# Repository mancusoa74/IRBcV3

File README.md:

# IRBcV3.1

Internet Relay Board Caricatore v3.1

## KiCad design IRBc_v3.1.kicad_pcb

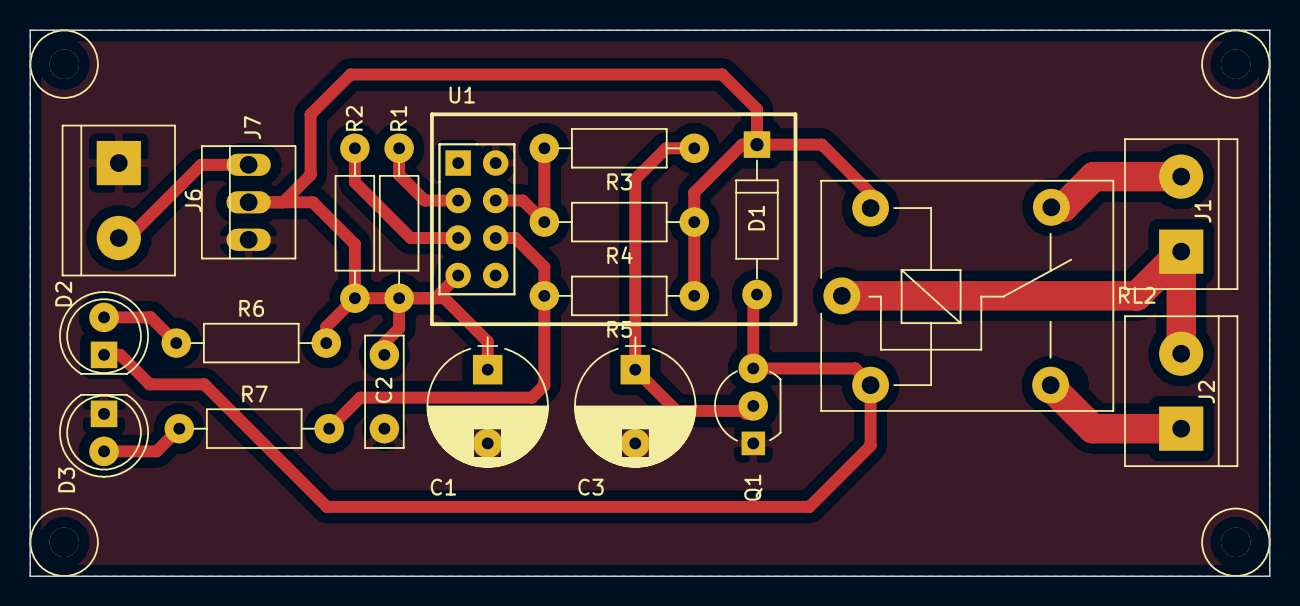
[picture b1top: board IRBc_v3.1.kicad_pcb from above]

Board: 2 copper layers, 84.0 x 37.0 mm, 20 parts (0 on the bottom side), 14 nets.

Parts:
C1: 100uF; CP_Radial_D8.0mm_P5.00mm
C2: 100nF; C_Disc_D7.5mm_W2.5mm_P5.00mm
C3: 220uF; CP_Radial_D8.0mm_P5.00mm
D1: 1N4007; D_A-405_P10.16mm_Horizontal
D2, D3: LED; LED_D5.0mm
J1, J2: bornier2
J6: Caricatore; bornier2
J7: AMS117 module; PINHEAD1-3
Q1: 2N2222; TO-92_Inline_Wide
R1, R2, R3, R4, R5: 2K2; R_Axial_DIN0207_L6.3mm_D2.5mm_P10.16mm_Horizontal
R6, R7: 100; R_Axial_DIN0207_L6.3mm_D2.5mm_P10.16mm_Horizontal
RL2: SRD-03VDC-SL-C; Relay_SPDT_SANYOU_SRD_Series_Form_C
U1: ESP-01v090; ESP-01

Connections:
+3V3: C1.1, C2.1, D1.1, J7.2, R1.2, R2.2, R4.1, R5.1, R6.2, RL2.5, U1.7
GND: C1.2, C2.2, C3.2, D3.1, J6.1, J7.1, Q1.1, U1.2
unnamed: C3.1, Q1.2, R3.1
unnamed: D1.2, D2.1, Q1.3, RL2.2
unnamed: D2.2, R6.1
unnamed: D3.2, R7.1
unnamed: J1.1, J2.2, RL2.1
unnamed: J1.2, RL2.4
unnamed: J2.1, RL2.3
unnamed: J6.2, J7.3
unnamed: R1.1, U1.3
unnamed: R2.1, U1.5
unnamed: R3.2, R4.2, U1.4
unnamed: R5.2, R7.2, U1.6

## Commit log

2017-10-02 IRBcV3.1
